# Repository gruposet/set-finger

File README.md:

*********************************************************************
****************************SET-FINGER*******************************
***********************GRUPO DE TRABALHO-SET*************************
*********************************************************************

GRUPO DE TRABALHO - SET

PROJETO SET-FINGER:

SET-FINGER é um projeto desenvolvido pelo Grupo de Trabalho - SET, com a solução de uma tranca elétrica por biometria para segurança do espaço de trabalho dos desenvolvedores e colaboradores do SET.

DESCRIÇÃO:

Os principais componentes do projeto são um Arduino Mega, um sensor
Biométrico, um teclado (4x3), shield Ethernet, relé, buzzer, display LCD e um LED.

O repositório é composto pelos diretórios arduino code, board, libraries,
nodefinger e schematic. Pelo arquivos componentesSetFinger.pdf e README.txt

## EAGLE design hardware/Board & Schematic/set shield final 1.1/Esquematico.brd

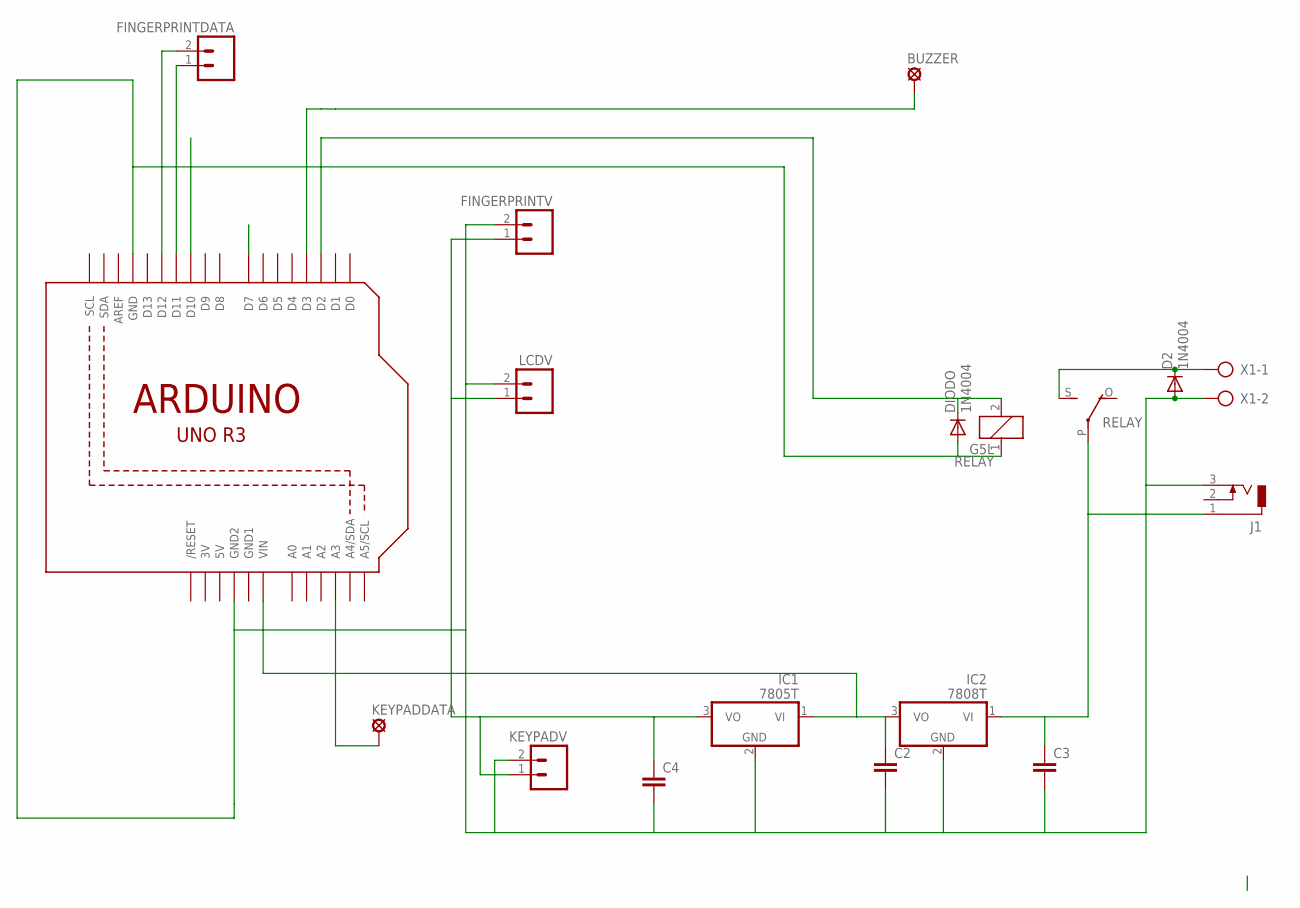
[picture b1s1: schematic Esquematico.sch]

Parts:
BUZZER: SE14
C2, C3, C4: C-EU025-030X050; C025-030X050
D2: 1N4004; DO41-10
DIODO: 1N4004; DO41-10
FINGERPRINTDATA: M02; 02P
FINGERPRINTV: M02; 02P
IC1: 7805T; TO220H
IC2: 7808T; TO220H
J1: DCJ0303
KEYPADDATA: SE14
KEYPADV: M02; 02P
LCDV: M02; 02P
Q1: ARDUINOR3-NOIOREF-NOTEXT; ARDUINOR3-NOTEXT-NOIOREF
RELAY: G5L; G5LE
X1: AK300/2

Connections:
3V: Q1.3V
5V: Q1.5V
GND1: Q1.GND1
unnamed: FINGERPRINTDATA.2, Q1.D12
unnamed: FINGERPRINTDATA.1, Q1.D11
unnamed: D2.C, RELAY.S, X1.1
unnamed: KEYPADDATA.MP, Q1.A3
unnamed: BUZZER.MP, Q1.D3
unnamed: C4.1, FINGERPRINTV.1, IC1.3 (VO), KEYPADV.1, LCDV.1
unnamed: DIODO.C, Q1.D2, RELAY.2
unnamed: DIODO.A, Q1.GND, RELAY.1
unnamed: C2.2, C3.2, C4.2, D2.A, FINGERPRINTV.2, IC1.2 (GND), IC2.2 (GND), J1.3, KEYPADV.2, LCDV.2, Q1.GND2, X1.2
unnamed: C2.1, IC1.1 (VI), IC2.3 (VO), Q1.VIN
unnamed: C3.1, IC2.1 (VI), J1.1, RELAY.P

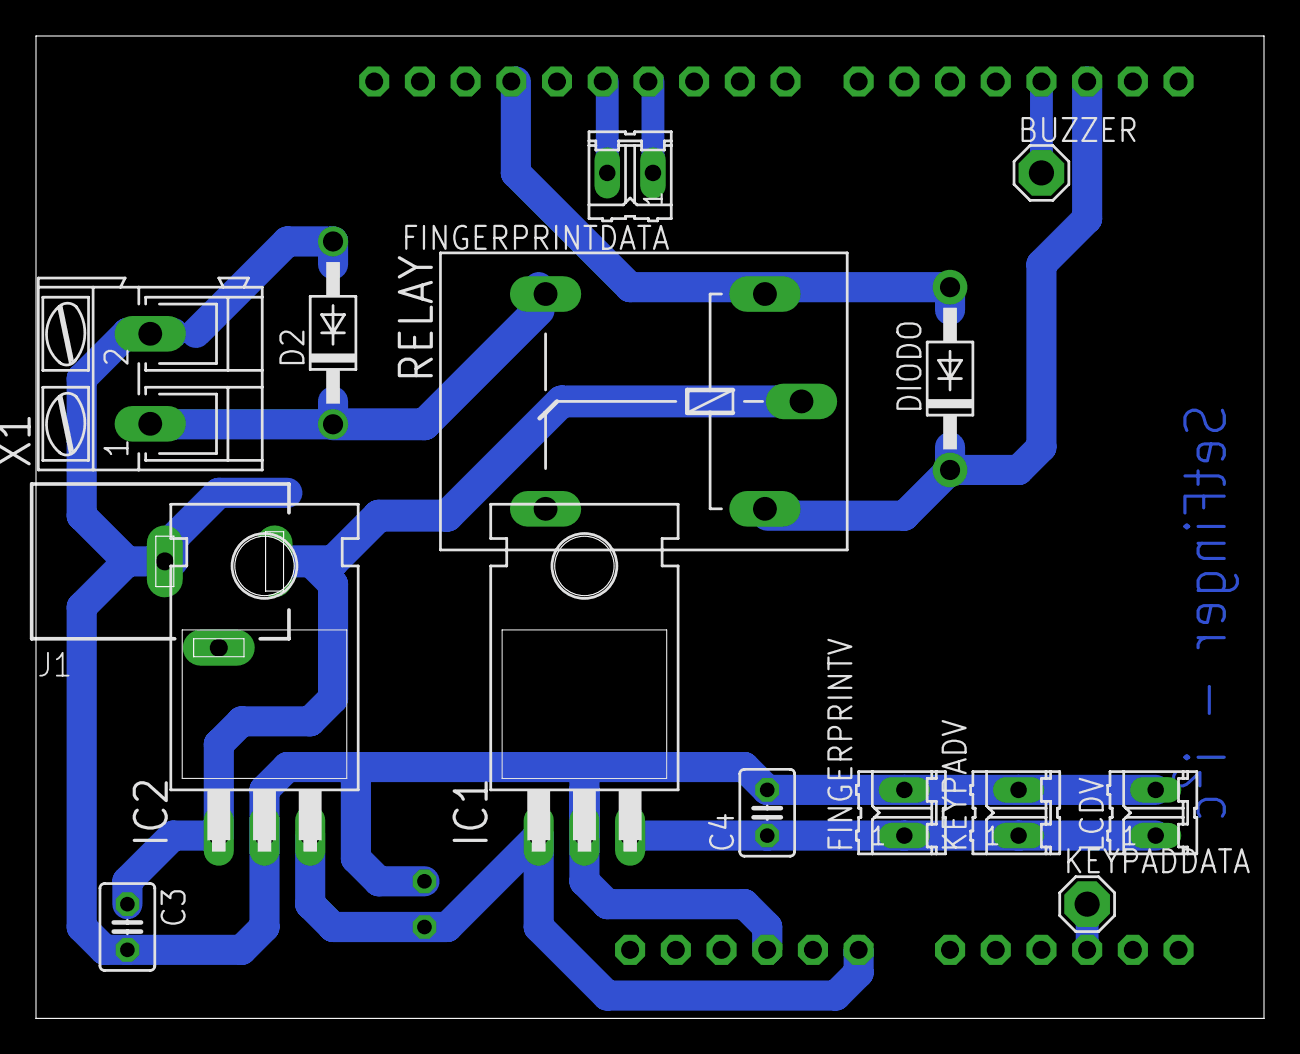
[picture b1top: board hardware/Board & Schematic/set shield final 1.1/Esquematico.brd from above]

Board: 2 copper layers, 68.2 x 54.6 mm, 17 parts (1 on the bottom side), 11 nets.

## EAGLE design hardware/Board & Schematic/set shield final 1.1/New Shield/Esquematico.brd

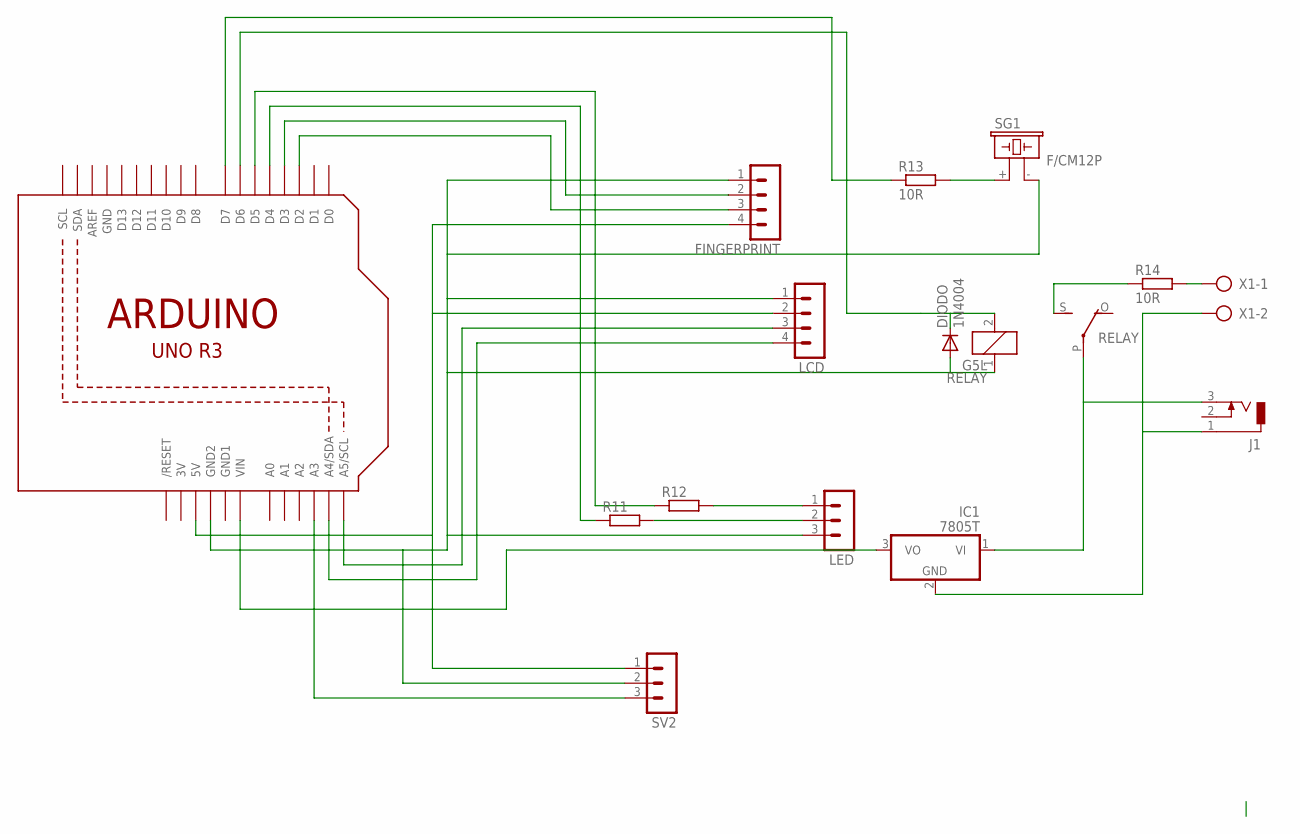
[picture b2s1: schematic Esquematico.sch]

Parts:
DIODO: 1N4004; DO41-10
FINGERPRINT: MA04-1
IC1: 7805T; TO220H
J1: DCJ0303
LCD: MA04-1
LED: MA03-1
Q1: ARDUINOR3-NOIOREF-NOTEXT; ARDUINOR3-NOTEXT-NOIOREF
R11, R12: R-EU_0309/10; 0309/10
R13: 10R; 0309/10
R14: 10R; P0817/22
RELAY: G5L; G5LE
SG1: F/CM12P
SV2: MA03-1
X1: AK300/2

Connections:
3V: Q1.3V
GND: Q1.GND
GND1: Q1.GND1
unnamed: FINGERPRINT.4, LCD.2, Q1.5V, SV2.1
unnamed: DIODO.A, FINGERPRINT.1, LCD.1, LED.3, Q1.GND2, RELAY.1, SG1.- (2), SV2.2
unnamed: FINGERPRINT.3, Q1.D2
unnamed: FINGERPRINT.2, Q1.D3
unnamed: LCD.3, Q1.A5 (A5/SCL)
unnamed: LCD.4, Q1.A4 (A4/SDA)
unnamed: DIODO.C, Q1.D6, RELAY.2
unnamed: Q1.D4, R11.1
unnamed: Q1.D5, R12.1
unnamed: Q1.D7, R13.1
unnamed: R14.2, X1.1
unnamed: IC1.2 (GND), J1.1, X1.2
unnamed: IC1.1 (VI), J1.3, RELAY.P
unnamed: R14.1, RELAY.S
unnamed: IC1.3 (VO), Q1.VIN
unnamed: R13.2, SG1.+ (1)
unnamed: LED.1, R12.2
unnamed: LED.2, R11.2
unnamed: Q1.A3, SV2.3

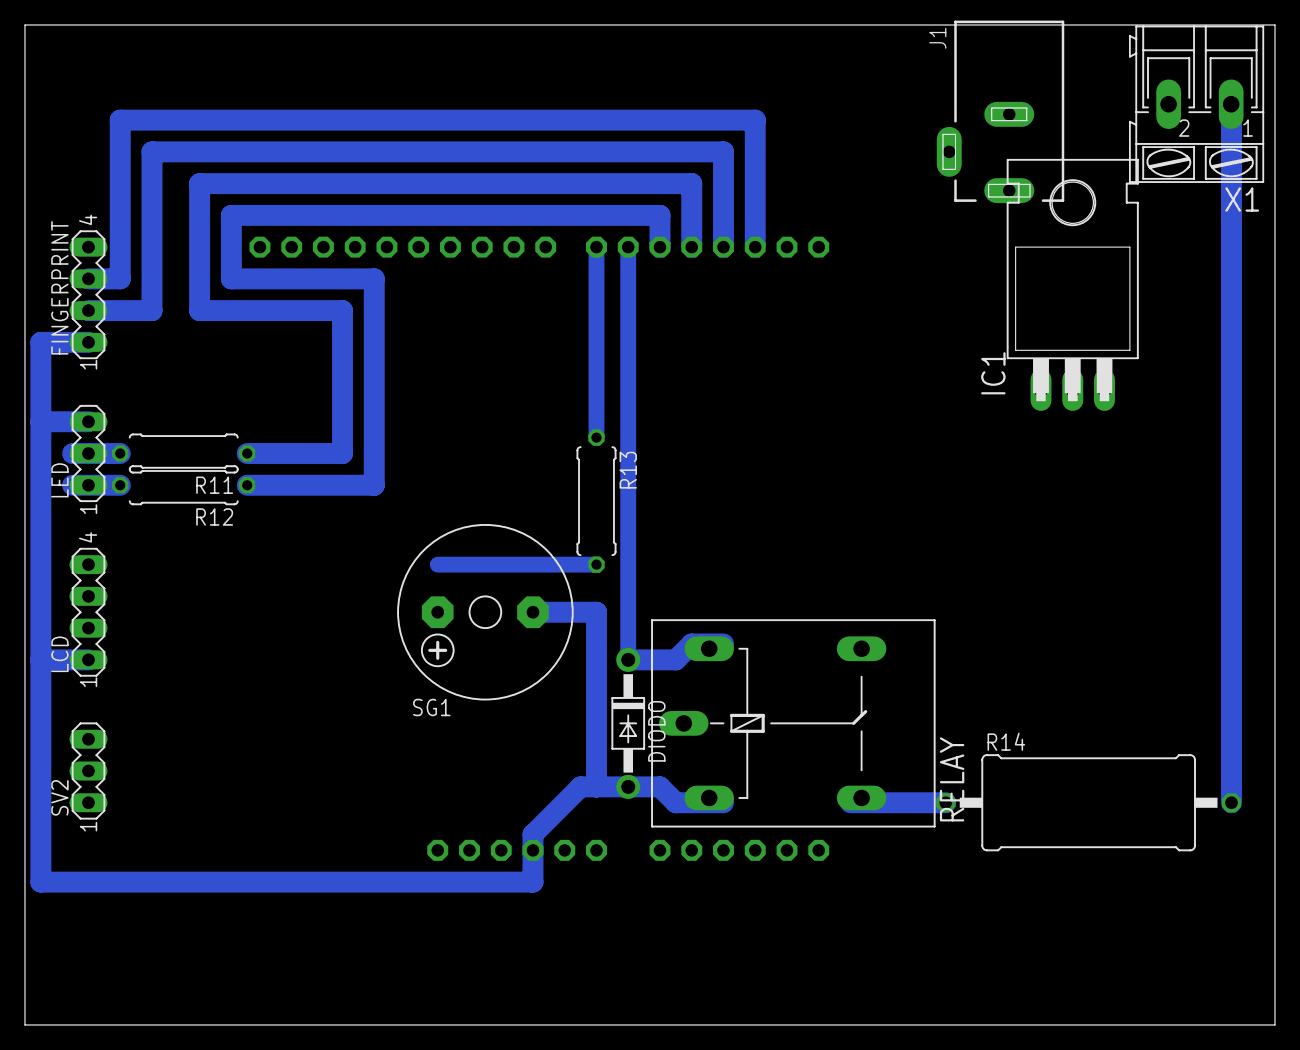
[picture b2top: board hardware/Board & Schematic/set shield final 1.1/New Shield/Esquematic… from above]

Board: 2 copper layers, 100.0 x 80.0 mm, 15 parts (0 on the bottom side), 19 nets.

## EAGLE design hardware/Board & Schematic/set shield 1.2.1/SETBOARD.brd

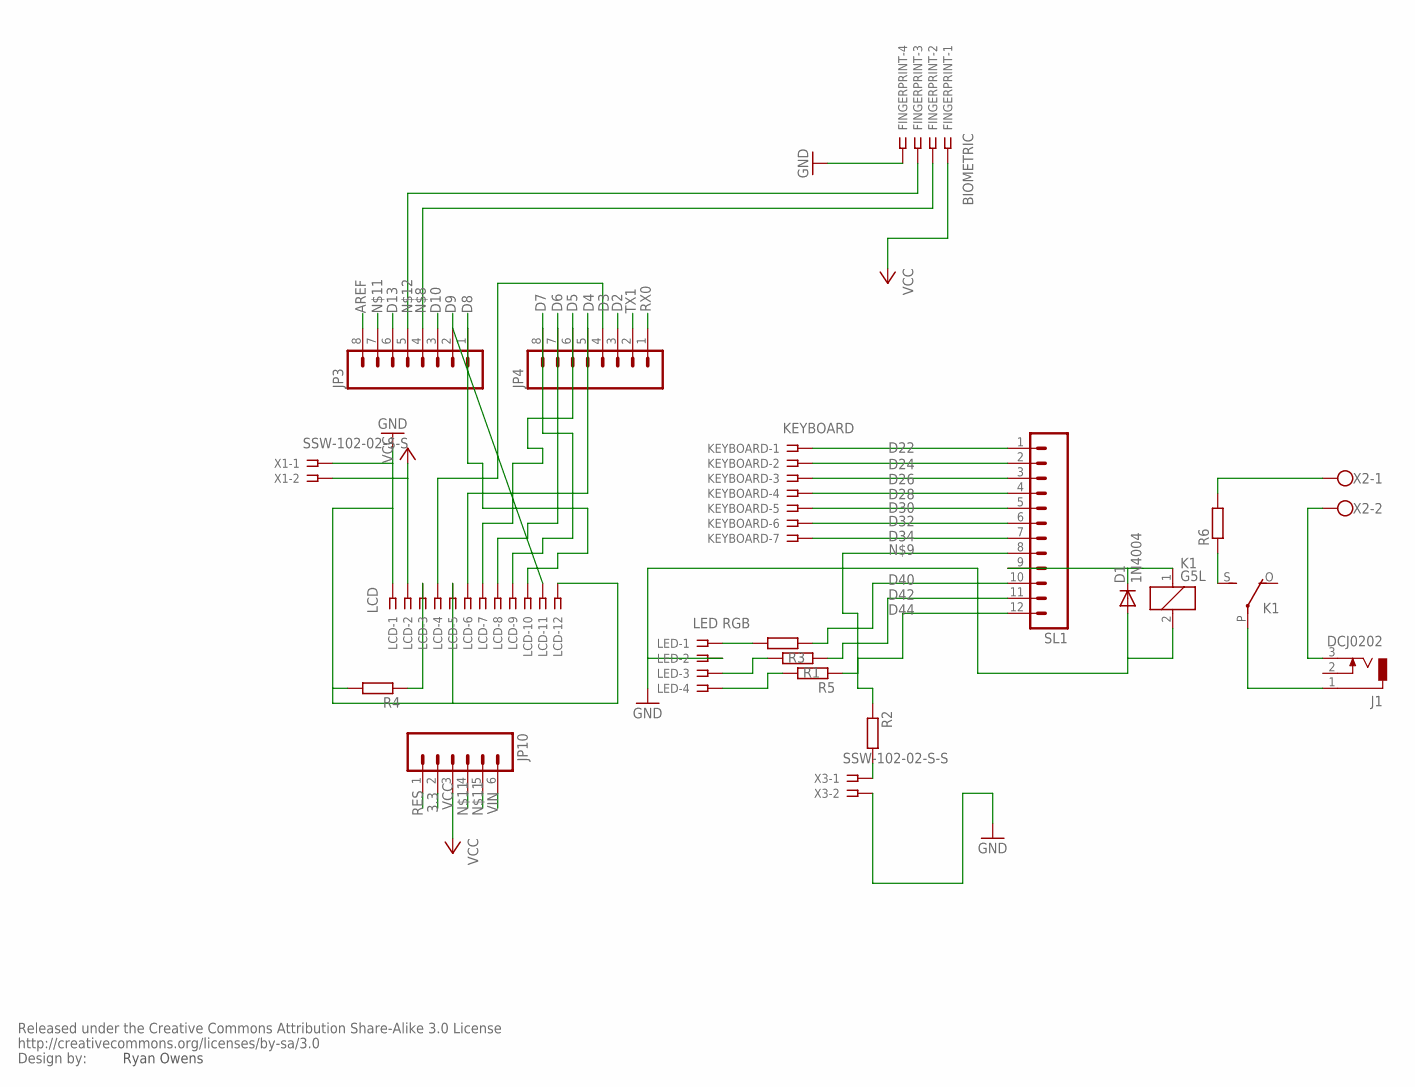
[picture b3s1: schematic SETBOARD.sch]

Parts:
D1: 1N4004; DO41-10
FINGERPRINT: BIOMETRIC; SSW-104-02-S-S
J1: DCJ0202
JP3, JP4: M08LOCK; 1X08_LOCK
JP10: M06LOCK; 1X06_LOCK
K1: G5L; G5LE
KEYBOARD: KEYBOARD; SSW-107-02-S-S
LCD: LCD; SSW-112-02-S-S
LED: LED RGB; SSW-104-02-S-S
R1, R2, R3, R4, R5: R0207/10; 0207/10
R6: R-EU_0817/22; P0817/22
SL1: M12; 12P
U$2: CREATIVE_COMMONS
X1, X3: SSW-102-02-S-S
X2: W237-102

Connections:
3.3: JP10.2
AREF: JP3.8
D2: JP4.3
D3: JP4.4, LCD.4
D4: JP4.5, LCD.6
D5: JP4.6, LCD.7
D6: JP4.7, LCD.8
D7: JP4.8, LCD.9
D8: JP3.1, LCD.10
D9: JP3.2, LCD.11
D10: JP3.3
D13: JP3.6
D22: KEYBOARD.1, SL1.1
D24: KEYBOARD.2, SL1.2
D26: KEYBOARD.3, SL1.3
D28: KEYBOARD.4, SL1.4
D30: KEYBOARD.5, SL1.5
D32: KEYBOARD.6, SL1.6
D34: KEYBOARD.7, SL1.7
D40: R3.1, SL1.10
D42: R1.1, SL1.11
D44: R5.1, SL1.12
unnamed: LCD.3, R4.1
unnamed: LED.1, R3.2
unnamed: LED.3, R1.2
unnamed: LED.4, R5.2
unnamed: R2.2, X3.1
unnamed: D1.C, K1.1, SL1.9
unnamed: FINGERPRINT.2, JP3.4
unnamed: R2.1, SL1.8
unnamed: D1.A, FINGERPRINT.4, JP3.7, JP10.4, JP10.5, K1.2, LCD.1, LCD.5, LCD.12, LED.2, R4.2, X1.1, X3.2
unnamed: FINGERPRINT.3, JP3.5
unnamed: K1.S, R6.1
unnamed: J1.3, X2.2
unnamed: J1.1, K1.P
unnamed: R6.2, X2.1
RES: JP10.1
RX0: JP4.1
TX1: JP4.2
VCC: FINGERPRINT.1, JP10.3, LCD.2, X1.2
VIN: JP10.6

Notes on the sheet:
Ryan Owens

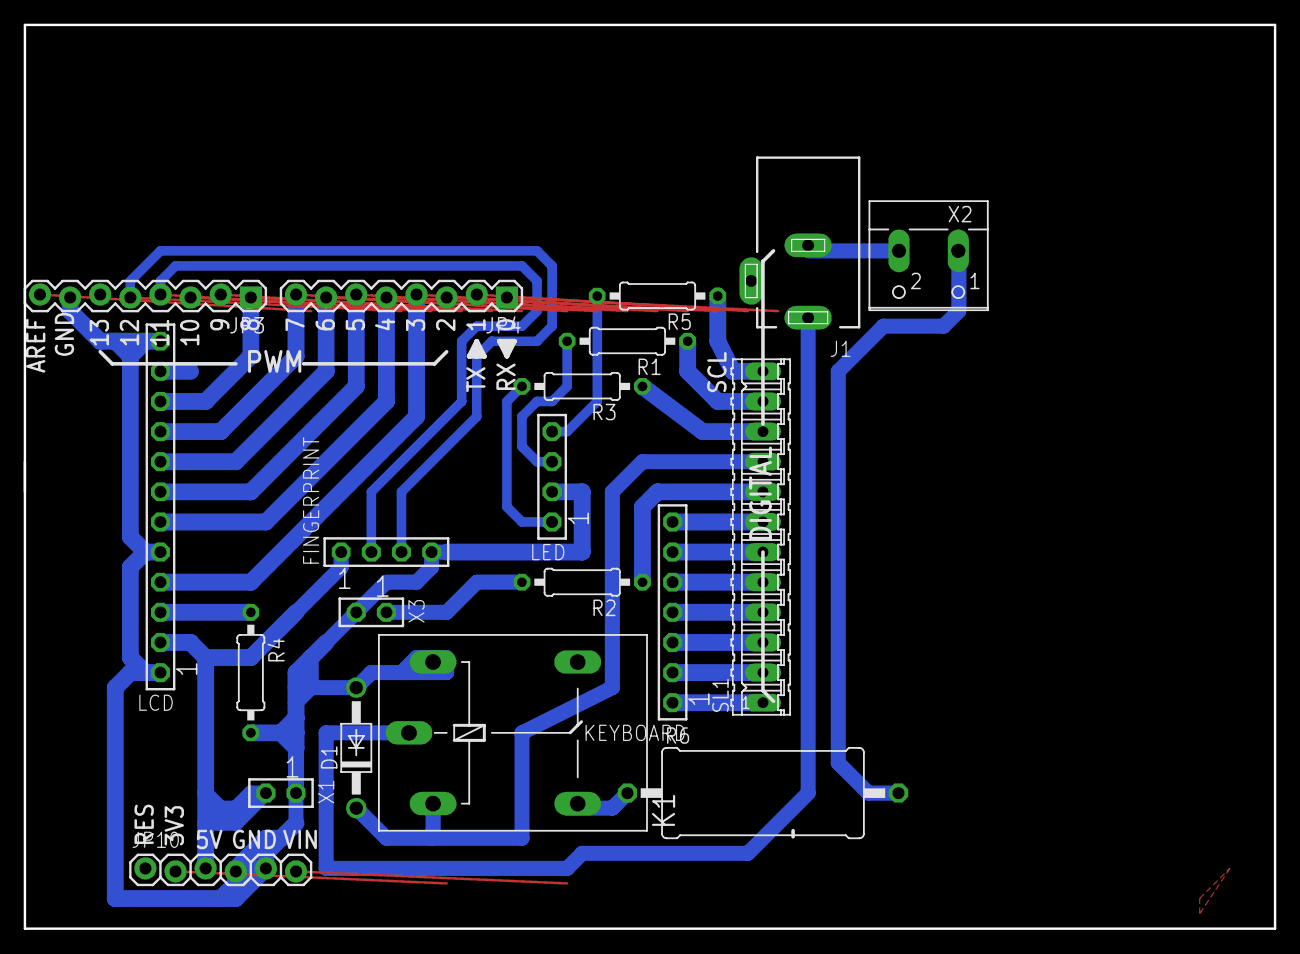
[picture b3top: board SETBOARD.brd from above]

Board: 2 copper layers, 105.4 x 76.2 mm, 21 parts (0 on the bottom side), 32 nets.

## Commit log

2015-09-09 Enviando
2015-09-15 Foi criado um diretório que contém os códigos de teste de cada componente do projeto
2015-09-15 atualização de repositório
2015-09-16 atualização repositório test
2015-09-16 nova versão de placa set shield e atualização do diretório test
2015-09-16 Foram adicionados as pastas .zip no diretório libraries, e foi adicionado o diretório de teste fingerprint no diretório tests
2015-09-16 atualização libraries: add os folders zipados
2015-09-16 Obs. no momento da importação de uma biblioteca para o arduino os arquivos compactados ou os folders devem conter somente letras em seu nome.
2015-09-18 atualização do código de teste keypad (correção de pinos). Atualização de diretório de servidor node para o setfinger
2015-09-23 Alguns arquivos foram editados, foi criado um diretório functions, setfinger_newcode e setfinger_oldcode
2015-09-23 O main code foi iniciado e é dada a largada!
2015-09-23 criação das funções de adição e leitura de digitais para o sensor fingerprint e atualização de diretório documentation
2015-09-24 atualização de códigos de teste do sensor fingerprint. Os códigos atualizados contém as funções definitivas que serão utilizadas no desenvolvimento do código do setfinger
2015-09-24 Novas funções adiconadas para o uso do módulo fingerprint
2015-09-24 atualização do código de teste do sensor fingerprint. Novo código completo com todas as funcionalidades integradas
2015-09-25 atualização de código tests>fingerprint
2015-09-28 Novas modificações, nada de se espantar.
2015-09-28 atualização do código de teste do teclado. reconfiguração da pinagem
2015-10-05 Foi adicionado o .ino no diretório tests/ para o teste do shield ethernet no servidor nodejs, lembrar de executar o setserver.js. Também foi atualizado o new setfinger.ino code
2015-10-15 atualização de códigos arduino (pinagem)
2015-10-16 SET-SERVER 2.0
2015-10-16 SET-FINGER 2.0
2015-10-16 Atualização README
2015-10-16 Atualização package.json
2015-10-20 bug fix
2015-11-06 ArduinoJson lib
2015-11-09 newcode->master
2015-11-09 Create teste
2015-11-13 atualização de código setfinger
2015-12-16 atualização de código node
2016-03-11 atualização esquemáticos (hardware)
2016-03-21 atualização servidor setserver/ node.js e página web
2016-03-23 código setfinger utilizando protocolo de comunicação i2c
2016-03-28 atualização código setfinger i2c - teclado funcionando
2016-03-28 correção de bug teclado i2c
2016-03-29 atualização código setfinger i2c - sem tempo de espera para retirar o dedo na hora do cadastro
2016-03-29 atualização código setSERVER - registro de nomes no registro de acessos (history)
2016-03-30 atualização código setserver 3.0 - alterações estrutura do BD
2016-03-31 Adição de nova placa setshiedl - i2c
2016-04-01 atualização código Setfinger-i2c
2016-04-27 Modificação na função leitura
    com a utilização do chip I²C PCF8574 para controlar nosso teclado, nossas funções de leitura de entradas do teclado matricial fora alteradas.
2016-05-18 adição do banco e página web

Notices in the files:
parts and their libraries:
SparkFun: Released under the Creative Commons Attribution Share-Alike 3.0 License
SparkFun: http://creativecommons.org/licenses/by-sa/3.0
